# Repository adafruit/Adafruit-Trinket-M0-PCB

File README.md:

## Adafruit Trinket M0 PCB

<a href="http://www.adafruit.com/products/3500"><br/>
Click here to purchase one from the Adafruit shop</a>

This is the CAD & PCB data for the Adafruit Trinket M0. PCB format is EagleCAD schematic and board layout

For more details, check out the product page at
* https://www.adafruit.com/products/3500

### Description

The Adafruit Trinket M0 may be small, but do not be fooled by its size! It's a tiny microcontroller board, built around the Atmel ATSAMD21, a little chip with a lot of power. We wanted to design a microcontroller board that was small enough to fit into any project, and low cost enough to use without hesitation. Perfect for when you don't want to give up your expensive dev-board and you aren't willing to take apart the project you worked so hard to design. It's our lowest-cost CircuitPython programmable board!

We've taken the same form factor we used for the original ATtiny85-based Trinket and gave it an upgrade. The Trinket M0 has swapped out the lightweight ATtiny85 for a ATSAMD21E18 powerhouse. It's just as small, and it's easier to use, so you can do more.

The most exciting part of the Trinket M0 is that while you can use it with the Arduino IDE, we are shipping it with CircuitPython on board. When you plug it in, it will show up as a very small disk drive with main.py on it. Edit main.py with your favorite text editor to build your project using Python, the most popular programming language. No installs, IDE or compiler needed, so you can use it on any computer, even ChromeBooks or computers you can't install software on. When you're done, unplug the Trinket M0 and your code will go with you. Please check out the Trinket M0 CircuitPython guide for a list of capabilities and quick-start code examples - CircuitPython is easier to code but not as low-level and complete as Arduino.

### License

Adafruit invests time and resources providing this open source design, please support Adafruit and open-source hardware by purchasing products from [Adafruit](https://www.adafruit.com)!

Designed by Limor Fried/Ladyada for Adafruit Industries.

Creative Commons Attribution/Share-Alike, all text above must be included in any redistribution. See license.txt for additional details.

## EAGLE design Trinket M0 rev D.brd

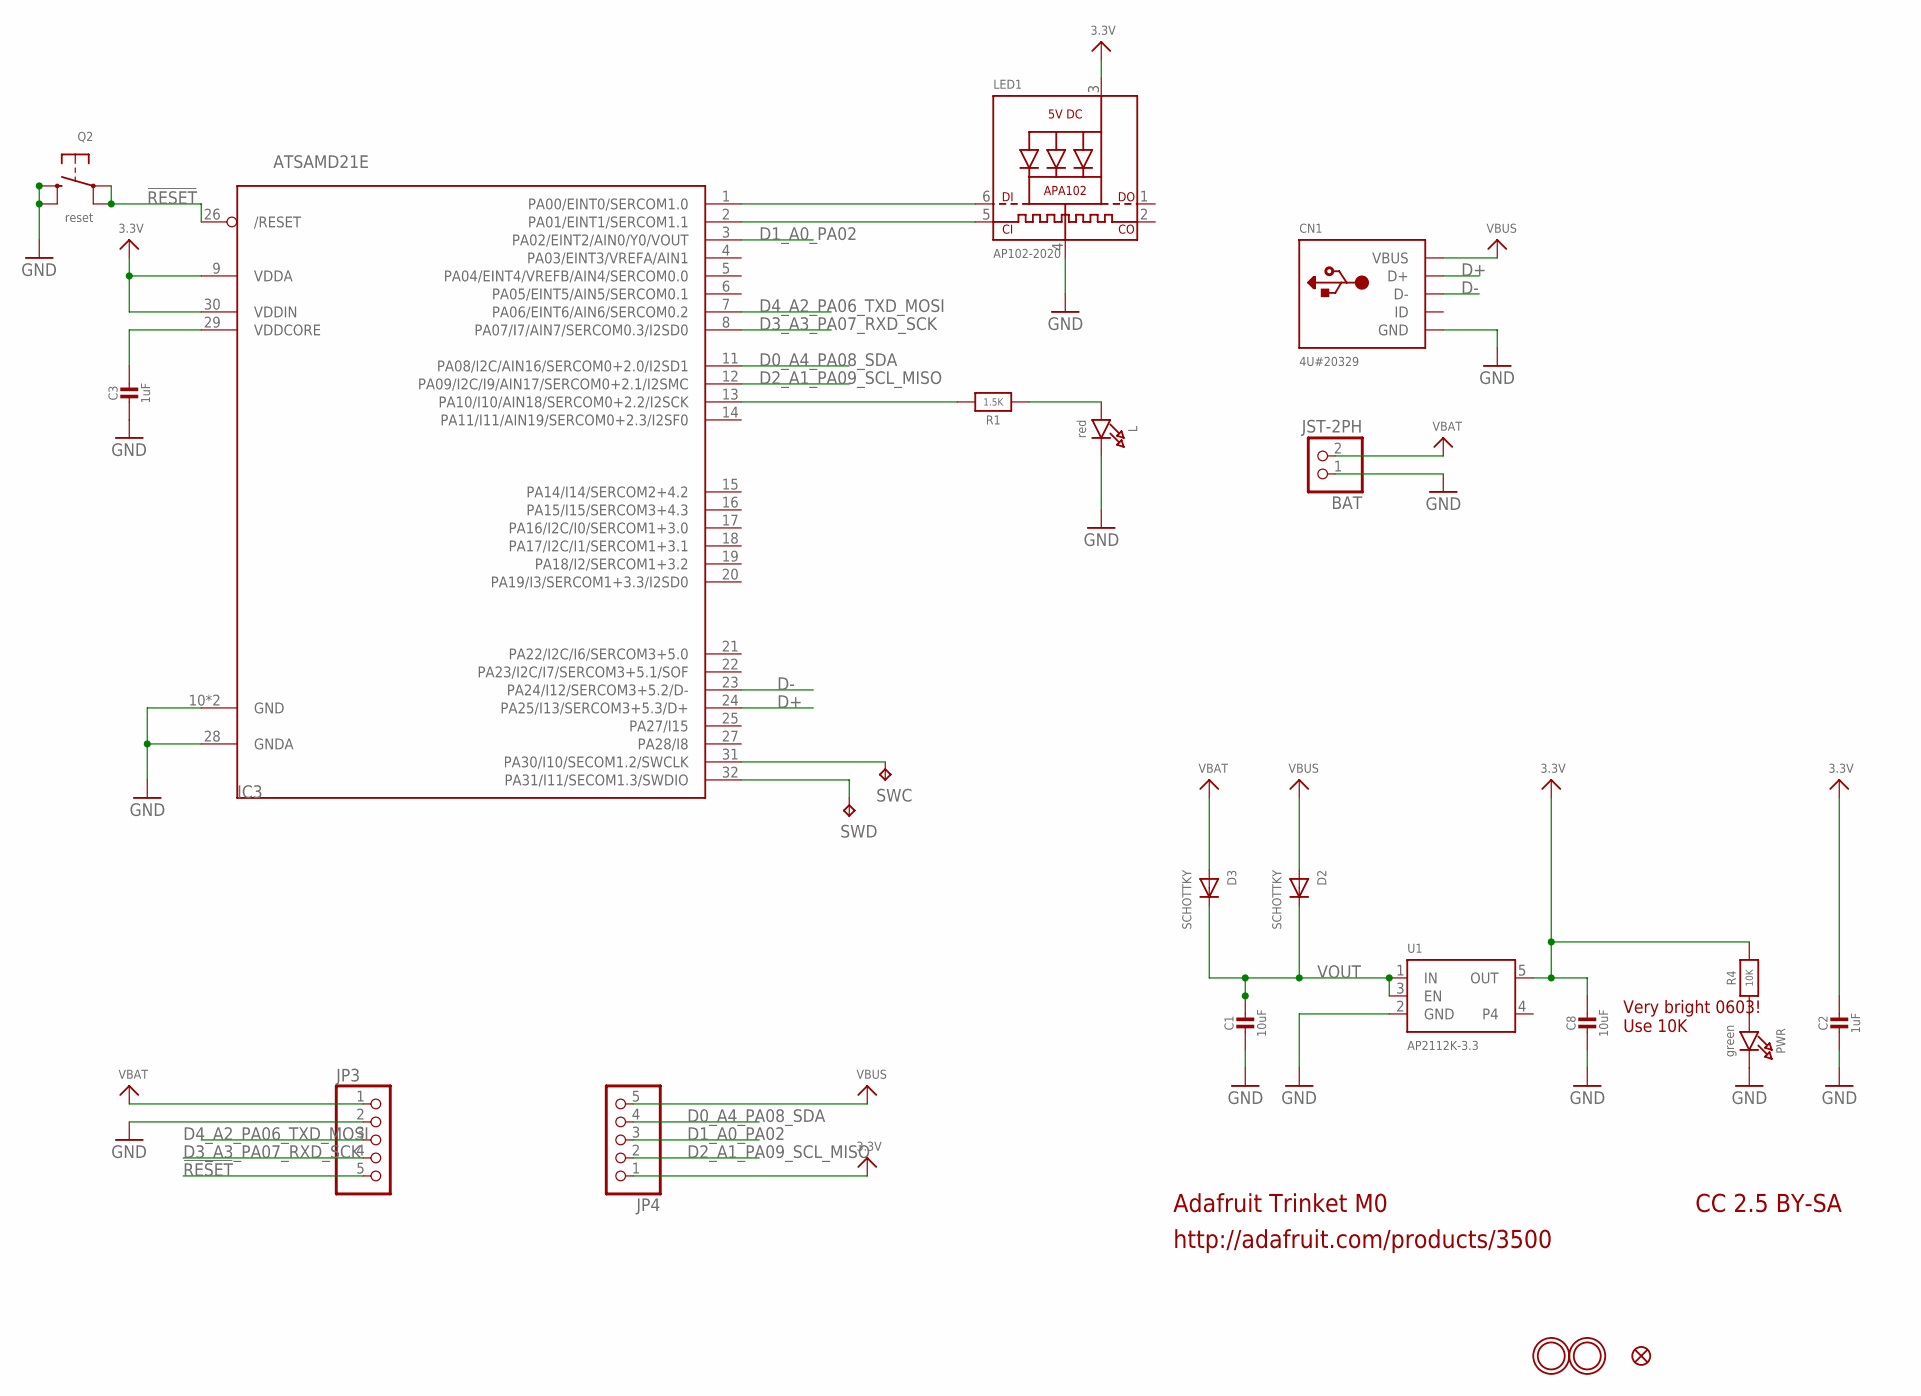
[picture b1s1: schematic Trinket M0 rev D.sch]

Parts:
BAT: JST-2PH; JSTPH2
C1, C8: 10uF; 0805-NO
C2, C3: 1uF; 0603-NO
CN1: 4U#20329; 4UCONN_20329_V2
D2, D3: SCHOTTKY; SOD-123FL
IC3: ATSAMD21E; QFN32_5MM
JP3, JP4: HEADER-1X576MIL; 1X05_ROUND_76
L: red; CHIPLED_0603_NOOUTLINE
LED1: AP102-2020; APA102_2020
PWR: green; CHIPLED_0603_NOOUTLINE
Q2: reset; BTN_KMR2_4.6X2.8
R1: 1.5K; 0603-NO
R4: 10K; 0603-NO
SWC: TPB1,27; B1,27
SWD: TPB1,27; B1,27
U1: AP2112K-3.3; SOT23-5
U$6: FIDUCIAL_1MM
U$8, U$9: MOUNTINGHOLE2.0; MOUNTINGHOLE_2.0_PLATED

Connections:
3.3V: C2.1, C8.1, IC3.9 (VDDA), IC3.30 (VDDIN), JP4.1, LED1.3 (VDD), R4.2, U1.5 (OUT)
!RESET: IC3.26 (/RESET), JP3.5, Q2.A, Q2.A' (P1)
A3: IC3.1 (PA00/EINT0/SERCOM1.0), LED1.6 (DI)
D0_A4_PA08_SDA: IC3.11 (PA08/I2C/AIN16/SERCOM0+2.0/I2SD1), JP4.4
D1_A0_PA02: IC3.3 (PA02/EINT2/AIN0/Y0/VOUT), JP4.3
D2_A1_PA09_SCL_MISO: IC3.12 (PA09/I2C/I9/AIN17/SERCOM0+2.1/I2SMC), JP4.2
D3_A3_PA07_RXD_SCK: IC3.8 (PA07/I7/AIN7/SERCOM0.3/I2SD0), JP3.4
D4_A2_PA06_TXD_MOSI: IC3.7 (PA06/EINT6/AIN6/SERCOM0.2), JP3.3
D+: CN1.D+, IC3.24 (PA25/I13/SERCOM3+5.3/D+)
D-: CN1.D-, IC3.23 (PA24/I12/SERCOM3+5.2/D-)
GND: BAT.1, C1.2, C2.2, C3.2, C8.2, CN1.BASE@1 (GND), CN1.BASE@2 (GND), CN1.GND, CN1.SPRT@1 (GND), CN1.SPRT@2 (GND), CN1.SPRT@3 (GND), CN1.SPRT@4 (GND), IC3.10 (GND), IC3.28 (GNDA), IC3.33 (GND), JP3.2, L.C, LED1.4 (GND), PWR.C, Q2.B (S), Q2.B' (S1), U1.2 (GND)
unnamed: L.A, R1.1
unnamed: IC3.13 (PA10/I10/AIN18/SERCOM0+2.2/I2SCK), R1.2
unnamed: IC3.31 (PA30/I10/SECOM1.2/SWCLK), SWC.TP
unnamed: IC3.32 (PA31/I11/SECOM1.3/SWDIO), SWD.TP
unnamed: PWR.A, R4.1
unnamed: IC3.2 (PA01/EINT1/SERCOM1.1), LED1.5 (CKI)
VBAT: BAT.2, D3.A, JP3.1
VBUS: CN1.VBUS, D2.A, JP4.5
VDDCORE: C3.1, IC3.29 (VDDCORE)
VOUT: C1.1, D2.C, D3.C, U1.1 (IN), U1.3 (EN)

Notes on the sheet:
Adafruit Trinket M0
http://adafruit.com/products/3500
CC 2.5 BY-SA
Very bright 0603! Use 10K

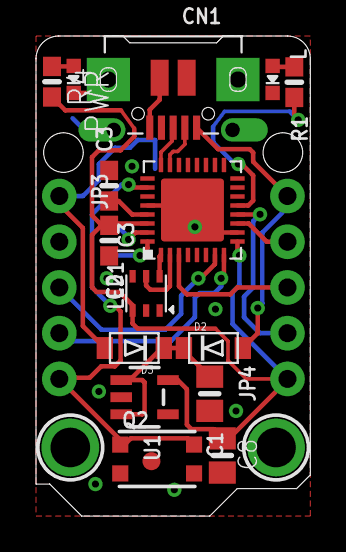
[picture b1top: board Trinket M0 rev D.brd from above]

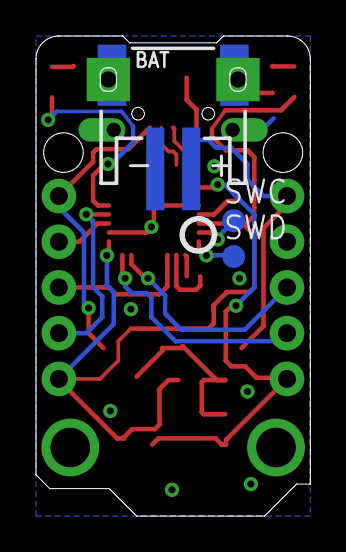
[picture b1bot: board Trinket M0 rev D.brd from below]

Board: 2 copper layers, 15.2 x 26.7 mm, 26 parts (5 on the bottom side), 21 nets.

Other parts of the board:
U$1: TRINKET_M0_BOTTOM
U$12: PCBFEAT-REV-040
U$20: TRINKET_M0_TOP

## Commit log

2017-08-23 kapow
2021-05-18 Add pinout PDF
2025-06-24 prettypins: explain pads better, correct error

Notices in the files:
parts and their libraries:
microbuilder: This work is placed in the public domain, and may be freely used for commercial and non-commercial work with the following conditions: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
